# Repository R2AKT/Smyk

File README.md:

License addendum - https://github.com/R2AKT/Smyk/blob/main/Addendum.txt

# Smyk

Sound synthesizer module (Smyk). For Mega-80 (Mega-580) DIY 8-bit micro-computer - https://github.com/R2AKT/Mega-80.

Generation of 3-channel 1-bit sound.

Based on 580VI53 (8253).

Status: In the process of testing.

Модуль синтезатора звукового (Smyk). Для самодельной 8-битной микро-ЭВМ - https://github.com/R2AKT/Mega-80.

Генерация 3-х канального 1-битного звука.

На основе 580ВИ53 (8253).

Статус: В процессе тестирования.

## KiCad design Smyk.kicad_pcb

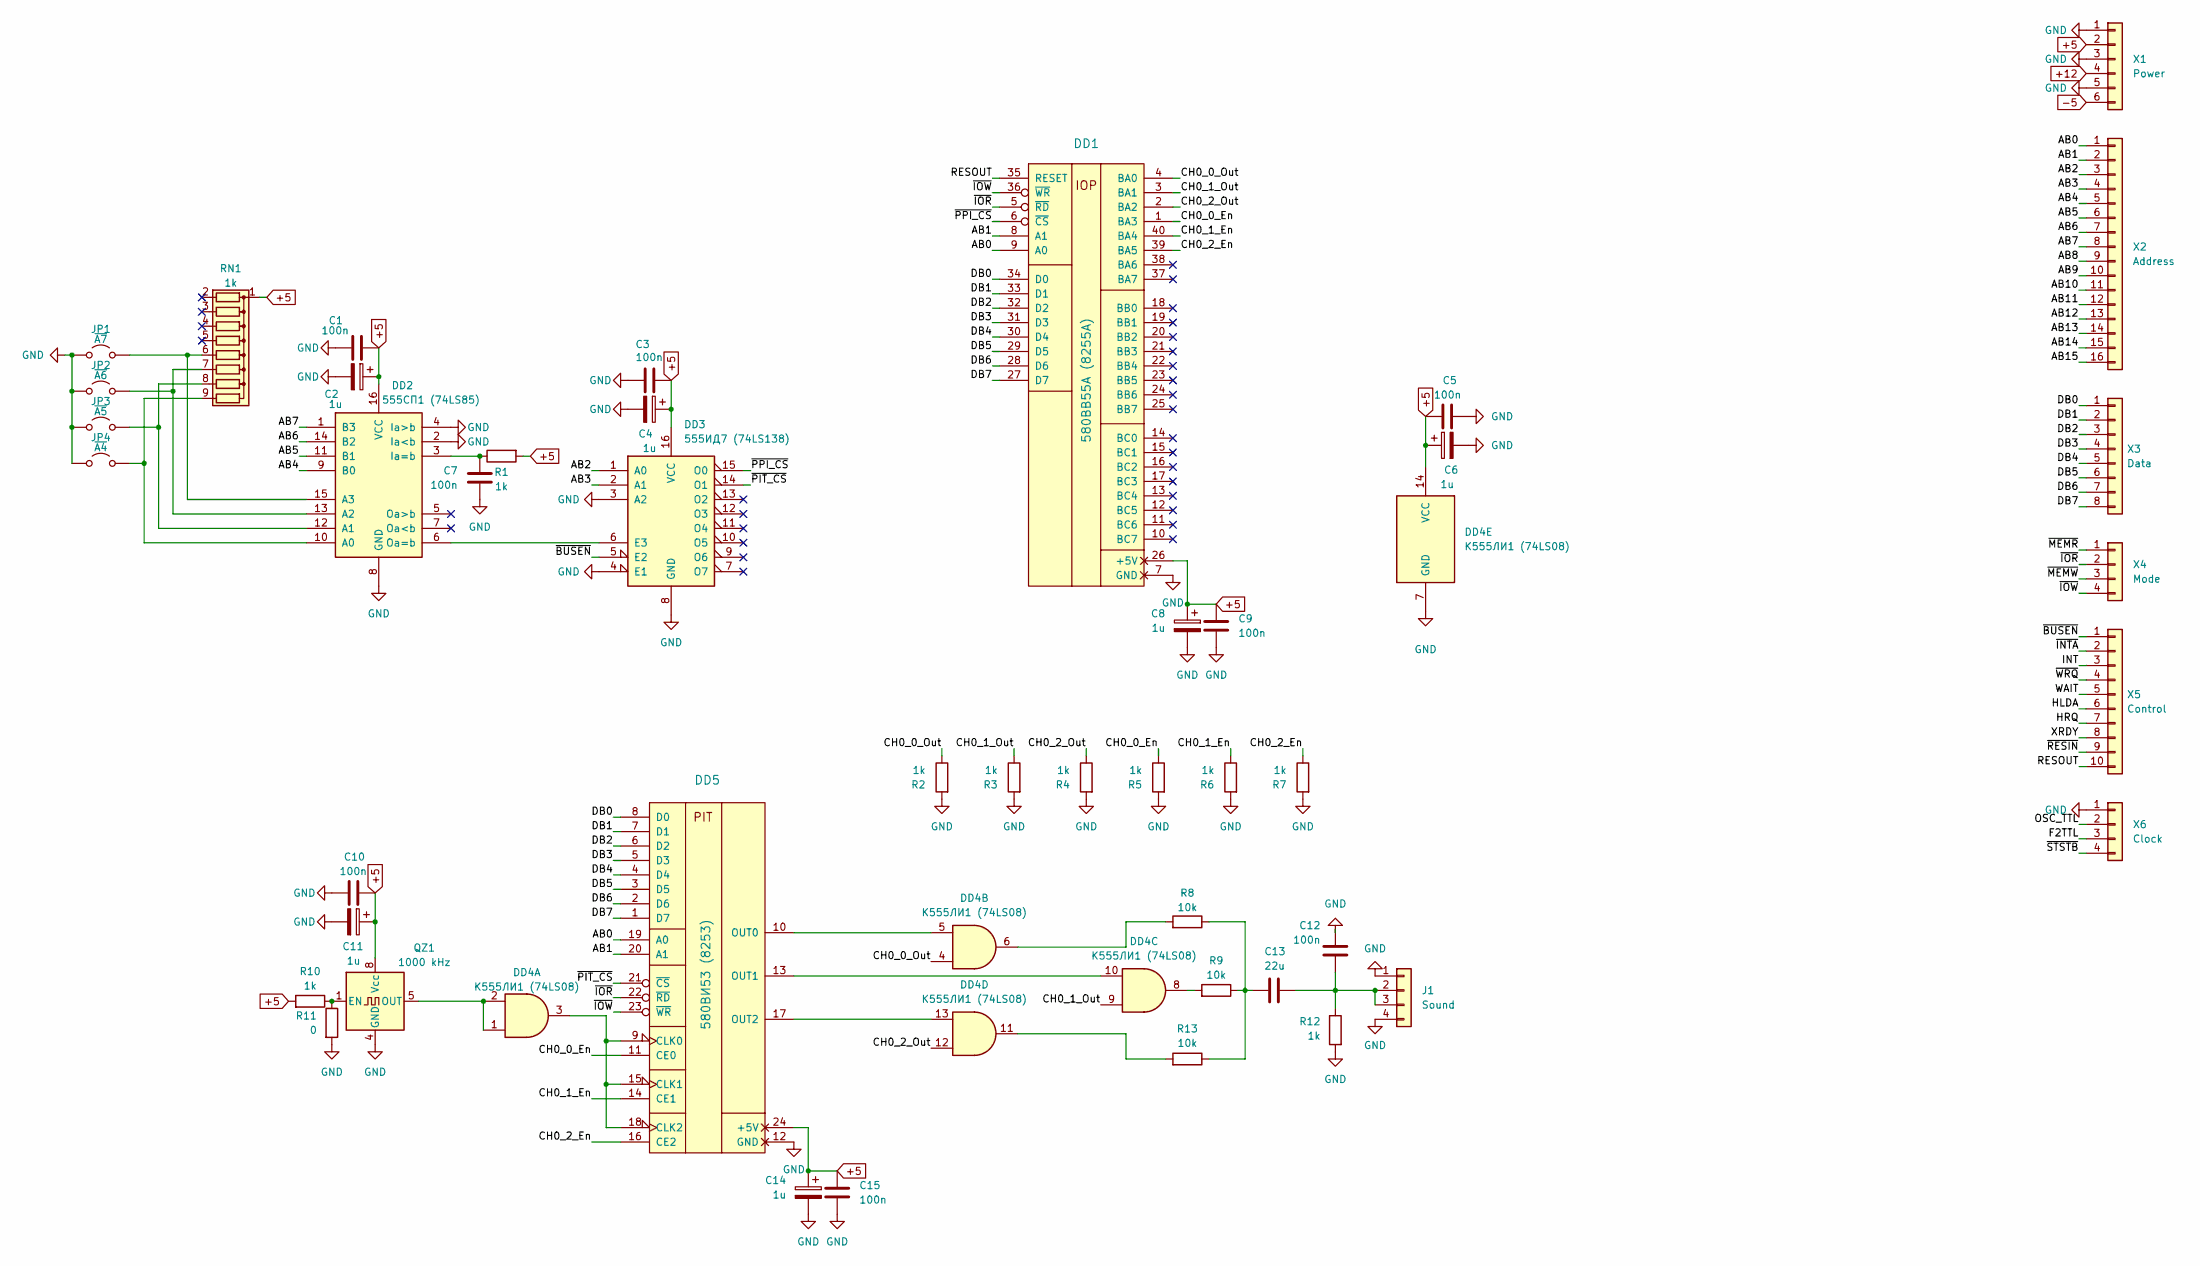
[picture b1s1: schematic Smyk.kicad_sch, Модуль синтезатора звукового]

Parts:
C1, C3, C5, C7, C9, C10, C12, C15: 100n; C_0805_2012Metric_Pad1.18x1.45mm_HandSolder
C2, C4, C6, C8, C11, C14: 1u; CP_EIA-3216-18_Kemet-A_Pad1.58x1.35mm_HandSolder
C13: 22u; C_0805_2012Metric_Pad1.18x1.45mm_HandSolder
DD1: 580ВВ55A (8255A); DIP-40_W15.24mm_Socket_LongPads
DD2: 555СП1 (74LS85); DIP-16_W7.62mm_Socket_LongPads
DD3: 555ИД7 (74LS138); DIP-16_W7.62mm_Socket_LongPads
DD4: К555ЛИ1 (74LS08); DIP-14_W7.62mm_Socket_LongPads
DD5: 580ВИ53 (8253); DIP-24_W15.24mm_Socket_LongPads
J1: Sound; PinHeader_1x04_P2.54mm_Vertical
JP1: ~{A7}; SolderJumper-2_P1.3mm_Open_RoundedPad1.0x1.5mm
JP2: ~{A6}; SolderJumper-2_P1.3mm_Open_RoundedPad1.0x1.5mm
JP3: ~{A5}; SolderJumper-2_P1.3mm_Open_RoundedPad1.0x1.5mm
JP4: ~{A4}; SolderJumper-2_P1.3mm_Open_RoundedPad1.0x1.5mm
QZ1: 1000 kHz; Oscillator_DIP-8_LargePads
R1, R2, R3, R4, R5, R6, R7, R10, R12: 1k; R_0805_2012Metric_Pad1.20x1.40mm_HandSolder
R8, R9, R13: 10k; R_0805_2012Metric_Pad1.20x1.40mm_HandSolder
R11: 0; R_0805_2012Metric_Pad1.20x1.40mm_HandSolder
RN1: 1k; R_Array_SIP9
X1: Power; PinHeader_1x06_P2.54mm_Vertical
X2: Address; PinHeader_1x16_P2.54mm_Vertical
X3: Data; PinHeader_1x08_P2.54mm_Vertical
X4: Mode; PinHeader_1x04_P2.54mm_Vertical
X5: Control; PinHeader_1x10_P2.54mm_Vertical
X6: Clock; PinHeader_1x04_P2.54mm_Vertical

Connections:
+5: C1.1, C2.1, C3.1, C4.1, C5.1, C6.1, C8.1, C9.1, C10.1, C11.1, C14.1, C15.1, DD1.26 (+5V), DD2.16 (VCC), DD3.16 (VCC), DD4.14 (VCC), DD5.24 (+5V), QZ1.8 (Vcc), R1.2, R10.2, RN1.1 (common), X1.2
+12: X1.4
-5: X1.6
/AB0: DD1.9 (A0), DD5.19 (A0), X2.1
/AB1: DD1.8 (A1), DD5.20 (A1), X2.2
/AB2: DD3.1 (A0), X2.3
/AB3: DD3.2 (A1), X2.4
/AB4: DD2.9 (B0), X2.5
/AB5: DD2.11 (B1), X2.6
/AB6: DD2.14 (B2), X2.7
/AB7: DD2.1 (B3), X2.8
/AB8: X2.9
/AB9: X2.10
/AB10: X2.11
/AB11: X2.12
/AB12: X2.13
/AB13: X2.14
/AB14: X2.15
/AB15: X2.16
/CH0_0_En: DD1.1 (BA3), DD5.11 (CE0), R5.1
/CH0_0_Out: DD1.4 (BA0), DD4.4, R2.1
/CH0_1_En: DD1.40 (BA4), DD5.14 (CE1), R6.1
/CH0_1_Out: DD1.3 (BA1), DD4.9, R3.1
/CH0_2_En: DD1.39 (BA5), DD5.16 (CE2), R7.1
/CH0_2_Out: DD1.2 (BA2), DD4.12, R4.1
/DB0: DD1.34 (D0), DD5.8 (D0), X3.1
/DB1: DD1.33 (D1), DD5.7 (D1), X3.2
/DB2: DD1.32 (D2), DD5.6 (D2), X3.3
/DB3: DD1.31 (D3), DD5.5 (D3), X3.4
/DB4: DD1.30 (D4), DD5.4 (D4), X3.5
/DB5: DD1.29 (D5), DD5.3 (D5), X3.6
/DB6: DD1.28 (D6), DD5.2 (D6), X3.7
/DB7: DD1.27 (D7), DD5.1 (D7), X3.8
/F2TTL: X6.3
/HLDA: X5.6
/HRQ: X5.7
/INT: X5.3
/OSC_TTL: X6.2
/RESOUT: DD1.35 (RESET), X5.10
/WAIT: X5.5
/XRDY: X5.8
/~BUSEN: DD3.5 (E2), X5.1
/~INTA: X5.2
/~IOR: DD1.5 (~RD), DD5.22 (~RD), X4.2
/~IOW: DD1.36 (~WR), DD5.23 (~WR), X4.4
/~MEMR: X4.1
/~MEMW: X4.3
/~PIT_CS: DD3.14 (O1), DD5.21 (~CS)
/~PPI_CS: DD1.6 (~CS), DD3.15 (O0)
/~RESIN: X5.9
/~STSTB: X6.4
/~WRQ: X5.4
GND: C1.2, C2.2, C3.2, C4.2, C5.2, C6.2, C7.2, C8.2, C9.2, C10.2, C11.2, C12.1, C14.2, C15.2, DD1.7 (GND), DD2.2 (Ia<b), DD2.4 (Ia>b), DD2.8 (GND), DD3.3 (A2), DD3.4 (E1), DD3.8 (GND), DD4.7 (GND), DD5.12 (GND), J1.1, J1.4, JP1.1 (A), JP2.1 (A), JP3.1 (A), JP4.1 (A), QZ1.4 (GND), R2.2, R3.2, R4.2, R5.2, R6.2, R7.2, R11.2, R12.2, X1.1, X1.3, X1.5, X6.1
unnamed: C13.2, R8.1, R9.1, R13.1
unnamed: DD2.10 (A0), JP4.2 (B), RN1.9 (R8)
unnamed: DD2.12 (A1), JP3.2 (B), RN1.8 (R7)
unnamed: DD2.13 (A2), JP2.2 (B), RN1.7 (R6)
unnamed: DD2.15 (A3), JP1.2 (B), RN1.6 (R5)
unnamed: C7.1, DD2.3 (Ia=b), R1.1
unnamed: DD2.6 (Oa=b), DD3.6 (E3)
unnamed: DD4.6, R8.2
unnamed: DD4.8, R9.2
unnamed: DD4.11, R13.2
unnamed: DD4.3, DD5.9 (CLK0), DD5.15 (CLK1), DD5.18 (CLK2)
unnamed: DD4.5, DD5.10 (OUT0)
unnamed: DD4.10, DD5.13 (OUT1)
unnamed: DD4.13, DD5.17 (OUT2)
unnamed: C12.2, C13.1, J1.2, J1.3, R12.1
unnamed: QZ1.1 (EN), R10.1, R11.1
unnamed: DD4.1, DD4.2, QZ1.5 (OUT)

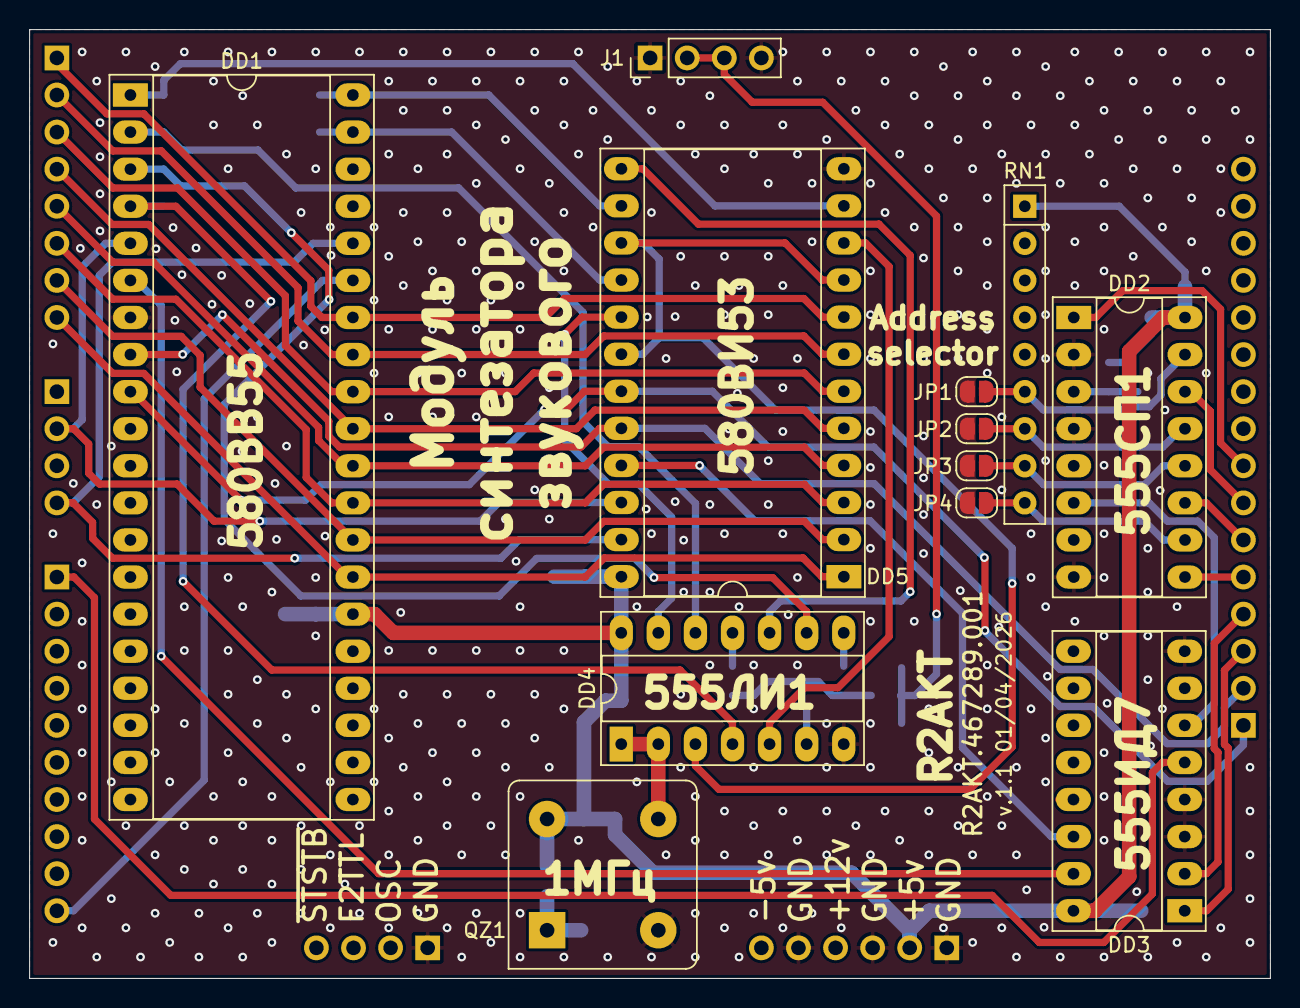
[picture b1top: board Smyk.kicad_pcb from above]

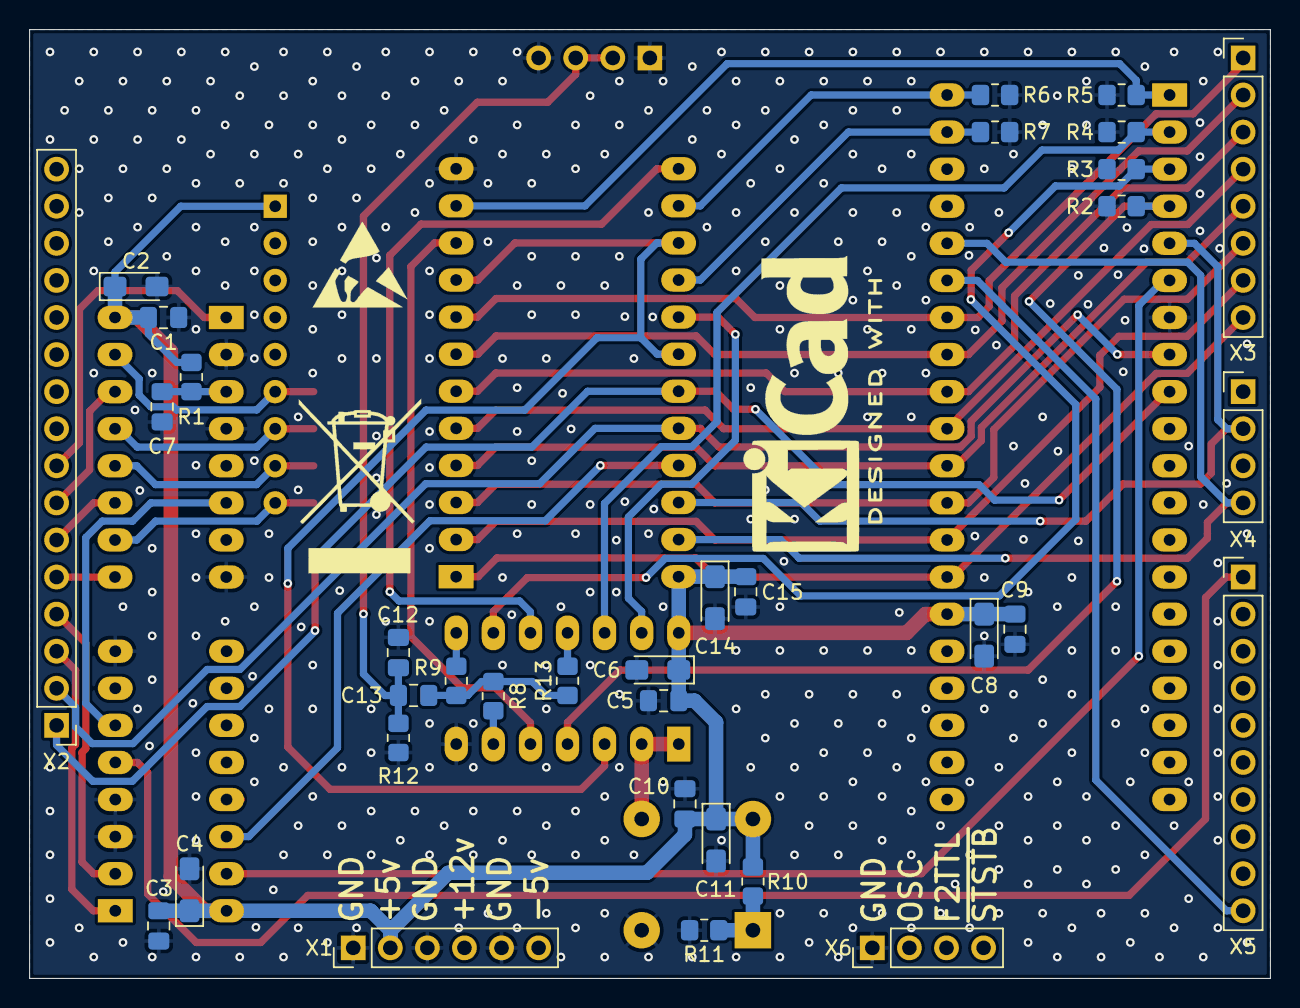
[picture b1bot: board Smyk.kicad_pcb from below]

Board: 2 copper layers, 85.0 x 65.0 mm, 46 parts (34 on the bottom side), 47 nets.

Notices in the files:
README.md:
License: MIT
